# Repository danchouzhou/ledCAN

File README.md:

# ledCAN
A multipurpose buck converter with CAN interface.

## Clone the project
This project work with M0A21BSP submodule from Nuvoton corporation. You need to initialize submodules by passing ``--recurse-submodules`` to the ``git clone`` command.
```
git clone https://github.com/MIH-pi/ledCAN.git --recurse-submodules
```

## Prepare environment
1. Installing tools
```
sudo apt install kicad build-essential gcc-arm-none-eabi libtool libusb-1.0-0-dev
```
2. Build and install customize version of OpenOCD for Nuvoton devices
```
git clone https://github.com/OpenNuvoton/OpenOCD-Nuvoton.git
cd OpenOCD-Nuvoton
./bootstrap
./configure --enable-nulink
make
sudo make install
```

## Credits
We are thankful that [Nuvoton corporation](https://www.nuvoton.com) (MCU),[PANJIT](https://www.panjit.com.tw) (MOSFET), [EDOM Technology](https://www.edomtech.com) (MPS MPQ4569GQ) and [Texas Instruments](https://ti.com) (CAN SBC) provide samples and technical support.

## Datasheet
[Nuvoton NuMicro M0A21/M0A23](https://www.nuvoton.com/export/resource-files/TRM_M0A21_M0A23_Series_EN_Rev1.02.pdf)

## Reference documents

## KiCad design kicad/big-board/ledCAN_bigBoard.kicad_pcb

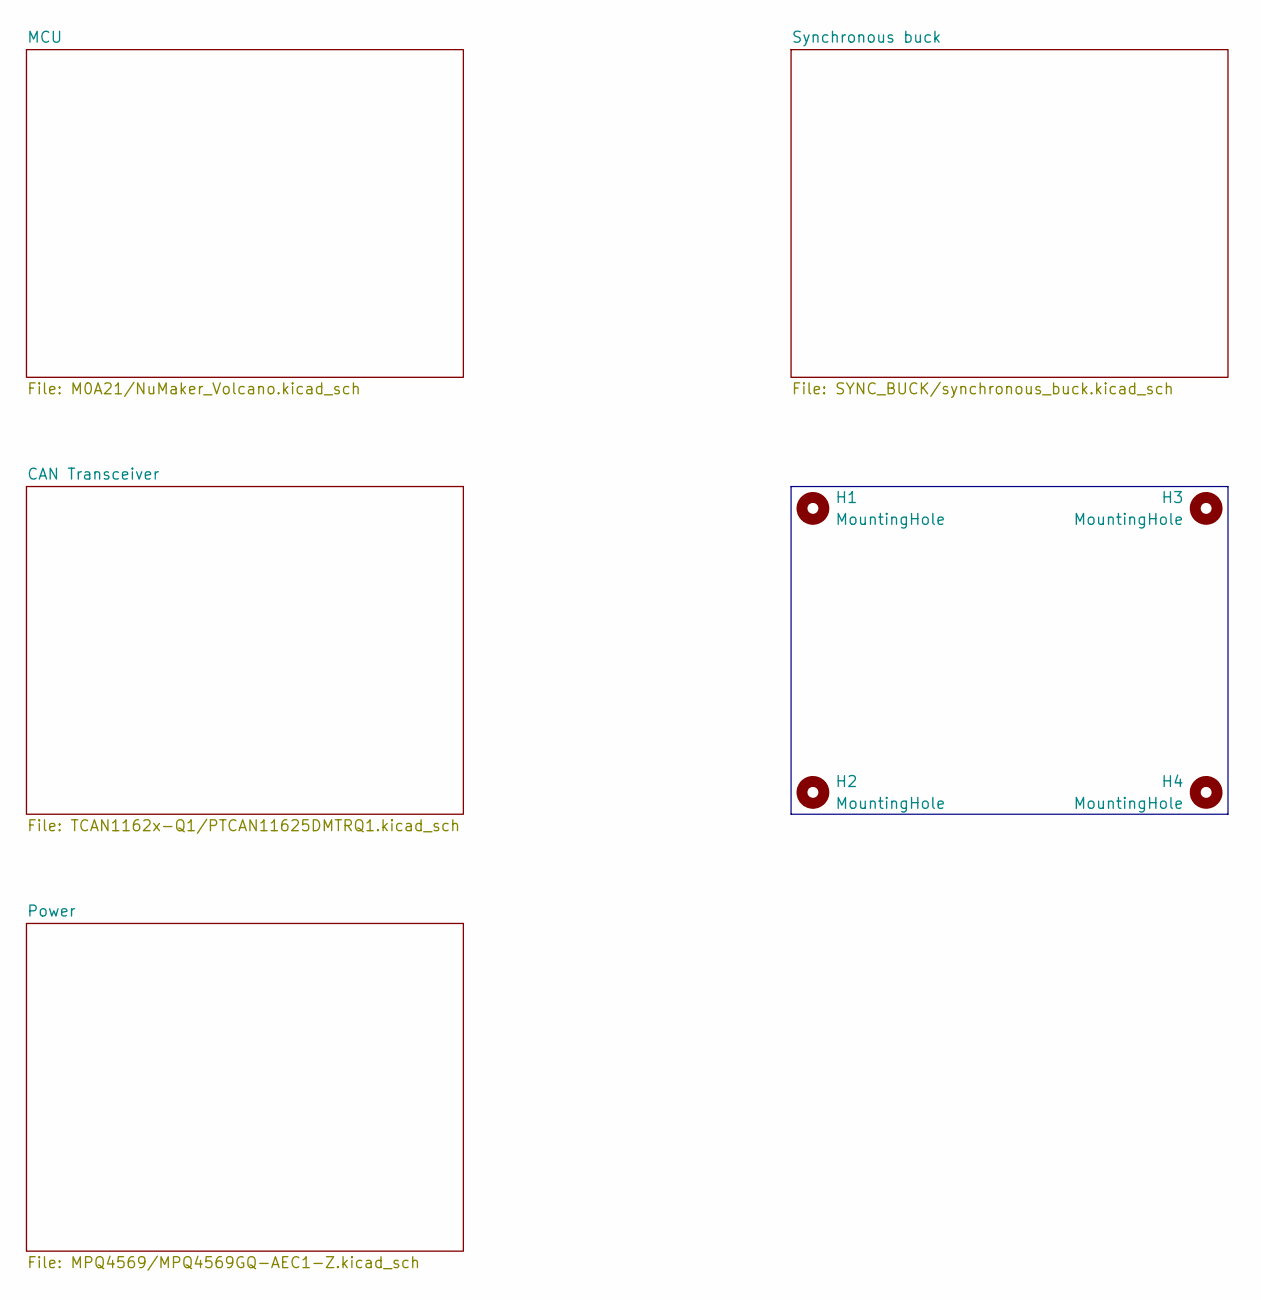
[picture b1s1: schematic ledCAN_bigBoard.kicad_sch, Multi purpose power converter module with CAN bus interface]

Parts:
H1, H2, H3, H4: MountingHole; MountingHole_3.2mm_M3

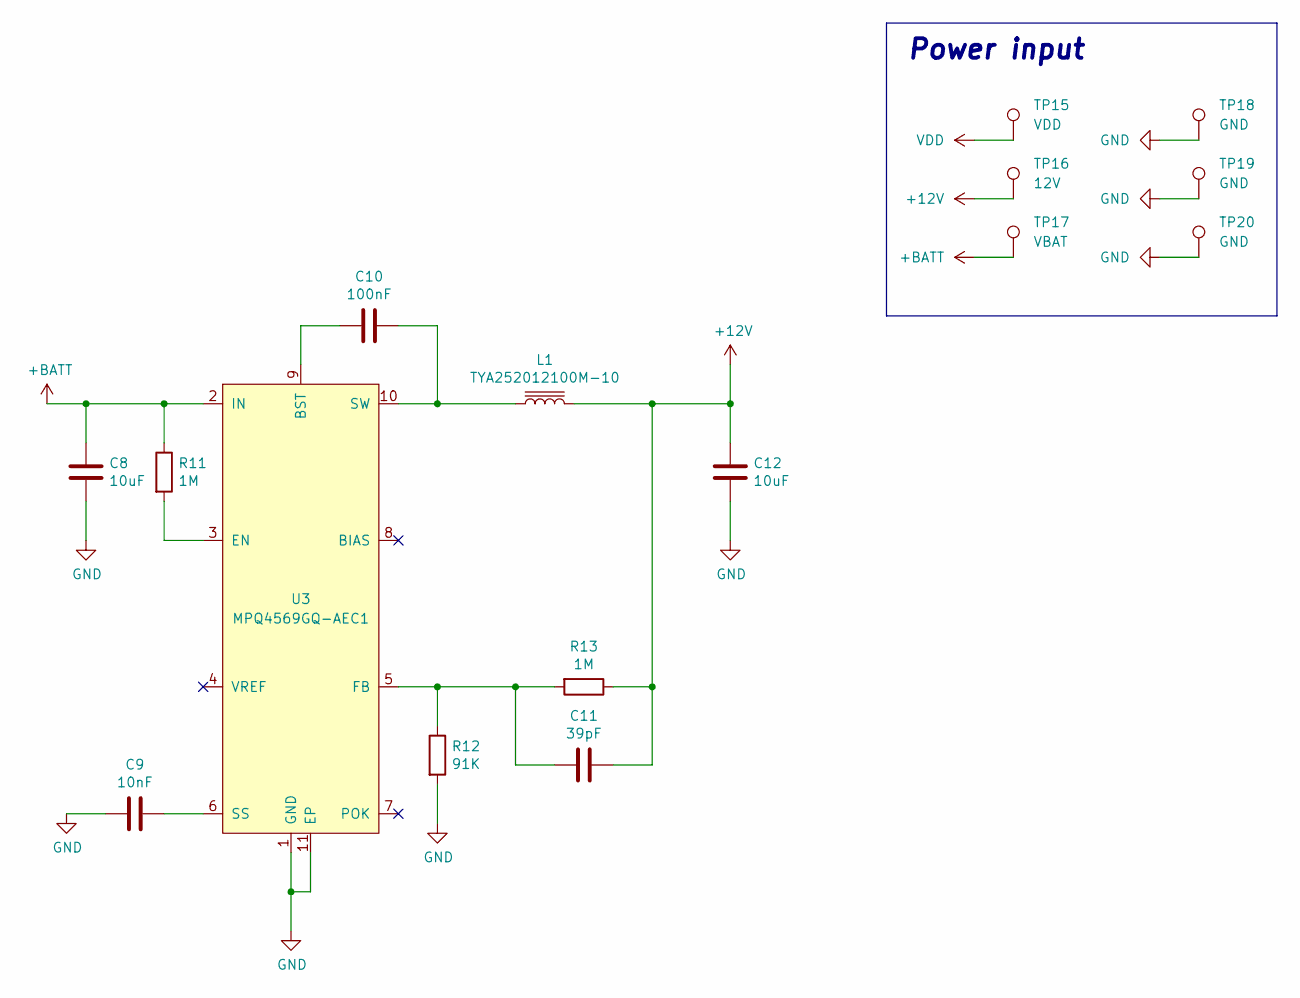
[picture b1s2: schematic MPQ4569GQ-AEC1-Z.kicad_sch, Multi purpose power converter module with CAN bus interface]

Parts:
C8: 10uF; C_1210_3225Metric
C9: 10nF; C_0603_1608Metric
C10: 100nF; C_0603_1608Metric
C11: 39pF; C_0603_1608Metric
C12: 10uF; C_0805_2012Metric
L1: TYA252012100M-10; tya252010-series
R11, R13: 1M; R_0603_1608Metric
R12: 91K; R_0603_1608Metric
TP15: VDD; TestPoint_Keystone_5005-5009_Compact
TP16: 12V; TestPoint_Keystone_5005-5009_Compact
TP17: VBAT; TestPoint_Keystone_5005-5009_Compact
TP18, TP19, TP20: GND; TestPoint_Keystone_5005-5009_Compact
U3: MPQ4569GQ-AEC1; QFN-10-1EP_3x3mm_P0.5mm_EP1.7x2.5mm

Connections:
+12V: C11.1, C12.1, L1.2, R13.1, TP16.1; also elsewhere on the board
+BATT: C8.1, R11.1, TP17.1, U3.2 (IN); also elsewhere on the board
unnamed: C9.1, U3.6 (SS)
unnamed: C10.1, L1.1, U3.10 (SW)
unnamed: C10.2, U3.9 (BST)
unnamed: C11.2, R12.1, R13.2, U3.5 (FB)
unnamed: R11.2, U3.3 (EN)

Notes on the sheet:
Power input

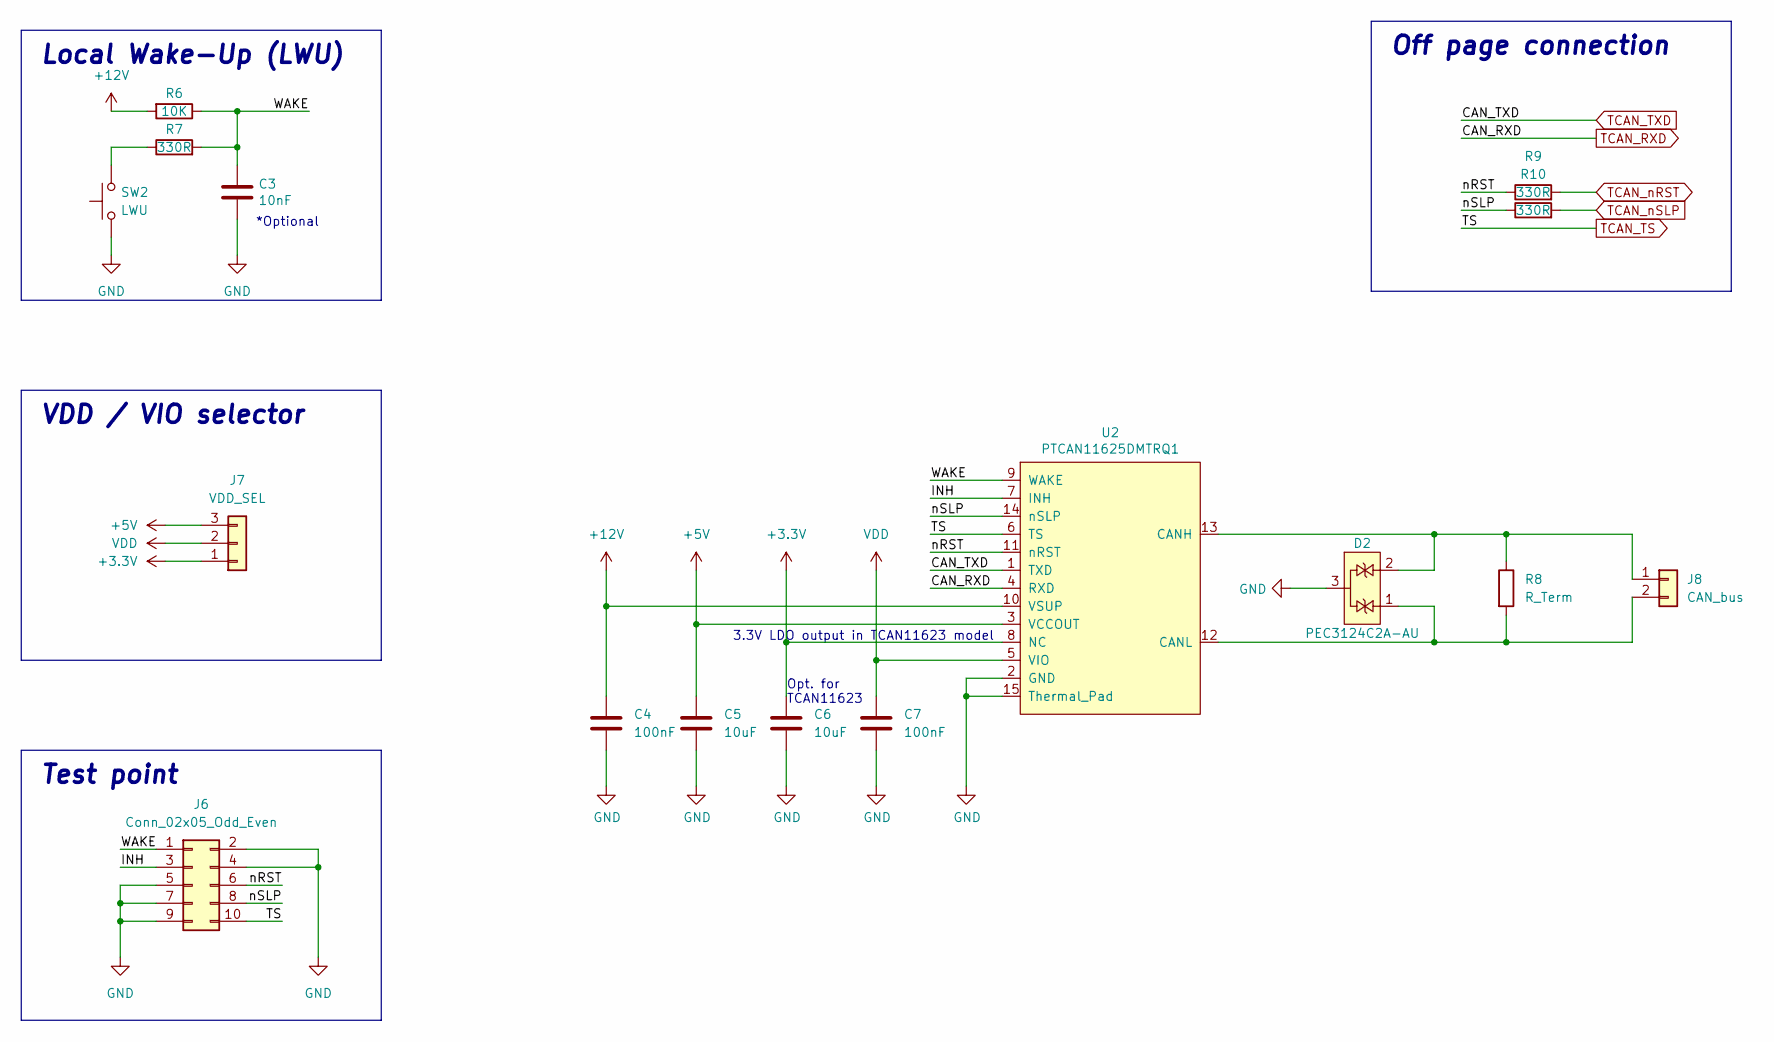
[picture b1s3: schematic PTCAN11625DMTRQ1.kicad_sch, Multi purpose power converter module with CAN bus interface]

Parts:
C3: 10nF; C_0603_1608Metric
C4, C7: 100nF; C_0603_1608Metric
C5, C6: 10uF; R_0805_2012Metric
D2: PEC3124C2A-AU; SOT-23; Manufacturer P/N PEC3124C2A-AU_R1_000A1
J6: Conn_02x05_Odd_Even; PinHeader_2x05_P2.54mm_Vertical
J7: VDD_SEL; PinHeader_1x03_P2.54mm_Vertical
J8: CAN_bus; PinHeader_1x02_P2.54mm_Vertical
R6: 10K; R_0603_1608Metric
R7, R9, R10: 330R; R_0603_1608Metric
R8: R_Term; R_1206_3216Metric
SW2: LWU; SW_PUSH_6mm
U2: PTCAN11625DMTRQ1; TI_VSON-14_4.5x3.0mm_DMT0014B_ThermalVias

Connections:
+3.3V: C6.1, J7.1, U2.8 (NC)
+5V: C5.1, J7.3, U2.3 (VCCOUT); also elsewhere on the board
+12V: C4.1, R6.2, U2.10 (VSUP); also elsewhere on the board
/CAN Transceiver/INH: J6.3, U2.7 (INH)
/CAN Transceiver/WAKE: C3.1, J6.1, R6.1, R7.2, U2.9 (WAKE)
/CAN Transceiver/nRST: J6.6, R9.1, U2.11 (nRST)
/CAN Transceiver/nSLP: J6.8, R10.1, U2.14 (nSLP)
unnamed: D2.1, J8.2, R8.2, U2.12 (CANL)
unnamed: D2.2, J8.1, R8.1, U2.13 (CANH)
unnamed: R7.1, SW2.2
TCAN_RXD: U2.4 (RXD); also elsewhere on the board
TCAN_TS: J6.10, U2.6 (TS); also elsewhere on the board
TCAN_TXD: U2.1 (TXD); also elsewhere on the board
TCAN_nRST: R9.2; also elsewhere on the board
TCAN_nSLP: R10.2; also elsewhere on the board

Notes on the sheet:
Local Wake-Up (LWU)
Test point
3.3V LDO output in TCAN11623 model
VDD / VIO selector
Off page connection
Opt. for TCAN11623
*Optional

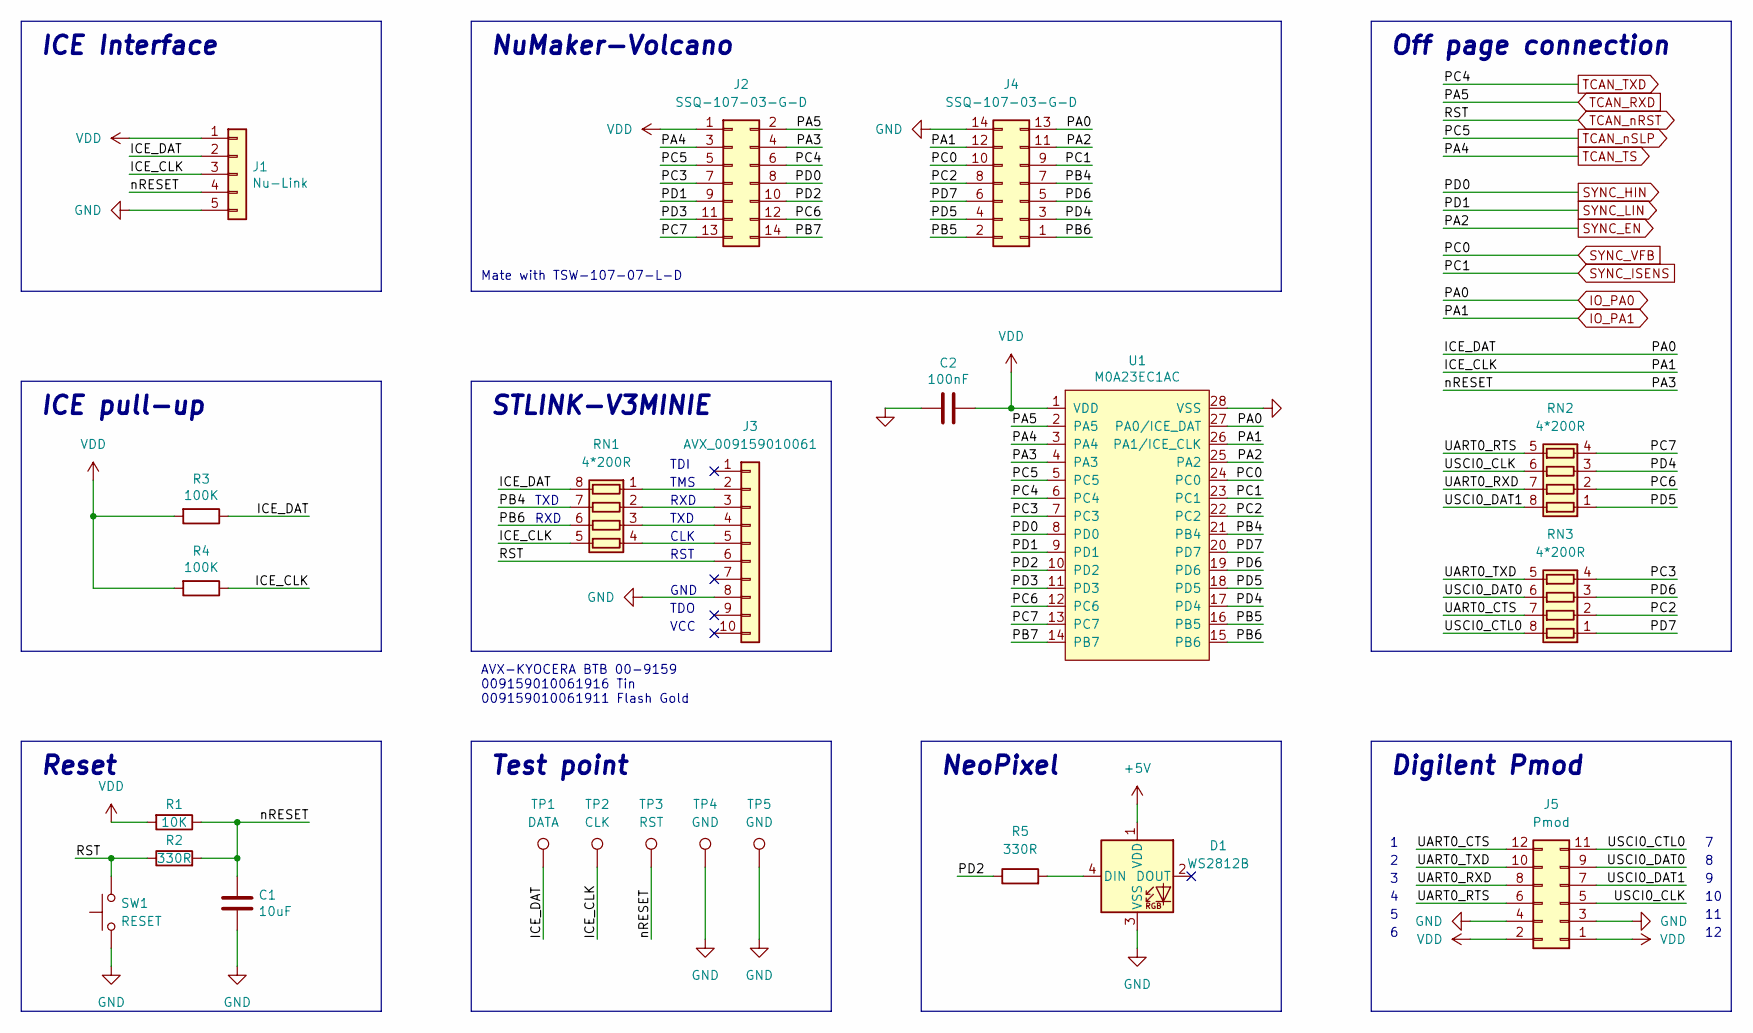
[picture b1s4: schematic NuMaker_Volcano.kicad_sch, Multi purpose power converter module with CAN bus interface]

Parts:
C1: 10uF; R_0603_1608Metric
C2: 100nF; C_0603_1608Metric
D1: WS2812B; LED_WS2812B_PLCC4_5.0x5.0mm_P3.2mm
J1: Nu-Link; PinHeader_1x05_P2.54mm_Vertical
J2, J4: SSQ-107-03-G-D; PinHeader_2x07_P2.54mm_Vertical
J3: AVX_009159010061; DebugEdge_2x05_Target
J5: Pmod; PinSocket_2x06_P2.54mm_Horizontal
R1: 10K; R_0603_1608Metric
R2, R5: 330R; R_0603_1608Metric
R3, R4: 100K; R_0603_1608Metric
RN1, RN2, RN3: 4*200R; R_Array_Convex_4x0603
SW1: RESET; SW_PUSH_6mm
TP1: DATA; TestPoint_Keystone_5005-5009_Compact
TP2: CLK; TestPoint_Keystone_5005-5009_Compact
TP3: RST; TestPoint_Keystone_5005-5009_Compact
TP4, TP5: GND; TestPoint_Keystone_5005-5009_Compact
U1: M0A23EC1AC; TSSOP-28_4.4x9.7mm_P0.65mm

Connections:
+5V: D1.1 (VDD); also elsewhere on the board
/MCU/PA3: C1.1, J1.4, J2.4, R1.1, R2.2, TP3.1, U1.4 (PA3)
/MCU/PB4: J4.7, RN1.7 (R2.2), U1.21 (PB4)
/MCU/PB5: J4.2, U1.16 (PB5)
/MCU/PB6: J4.1, RN1.6 (R3.2), U1.15 (PB6)
/MCU/PB7: J2.14, U1.14 (PB7)
/MCU/PC2: J4.8, RN3.2 (R2.1), U1.22 (PC2)
/MCU/PC3: J2.7, RN3.4 (R4.1), U1.7 (PC3)
/MCU/PC6: J2.12, RN2.2 (R2.1), U1.12 (PC6)
/MCU/PC7: J2.13, RN2.4 (R4.1), U1.13 (PC7)
/MCU/PD2: J2.10, R5.1, U1.10 (PD2)
/MCU/PD3: J2.11, U1.11 (PD3)
/MCU/PD4: J4.3, RN2.3 (R3.1), U1.17 (PD4)
/MCU/PD5: J4.4, RN2.1 (R1.1), U1.18 (PD5)
/MCU/PD6: J4.5, RN3.3 (R3.1), U1.19 (PD6)
/MCU/PD7: J4.6, RN3.1 (R1.1), U1.20 (PD7)
/MCU/UART0_CTS: J5.12, RN3.7 (R2.2)
/MCU/UART0_RTS: J5.6, RN2.5 (R4.2)
/MCU/UART0_RXD: J5.8, RN2.7 (R2.2)
/MCU/UART0_TXD: J5.10, RN3.5 (R4.2)
/MCU/USCI0_CLK: J5.5, RN2.6 (R3.2)
/MCU/USCI0_CTL0: J5.11, RN3.8 (R1.2)
/MCU/USCI0_DAT0: J5.9, RN3.6 (R3.2)
/MCU/USCI0_DAT1: J5.7, RN2.8 (R1.2)
IO_PA0: J1.2, J4.13, R3.1, RN1.8 (R1.2), TP1.1, U1.27 (PA0/ICE_DAT); also elsewhere on the board
IO_PA1: J1.3, J4.12, R4.1, RN1.5 (R4.2), TP2.1, U1.26 (PA1/ICE_CLK); also elsewhere on the board
unnamed: D1.4 (DIN), R5.2
unnamed: J3.2, RN1.1 (R1.1)
unnamed: J3.3, RN1.2 (R2.1)
unnamed: J3.4, RN1.3 (R3.1)
unnamed: J3.5, RN1.4 (R4.1)
SYNC_EN: J4.11, U1.25 (PA2); also elsewhere on the board
SYNC_HIN: J2.8, U1.8 (PD0); also elsewhere on the board
SYNC_ISENS: J4.9, U1.23 (PC1); also elsewhere on the board
SYNC_LIN: J2.9, U1.9 (PD1); also elsewhere on the board
SYNC_VFB: J4.10, U1.24 (PC0); also elsewhere on the board
TCAN_RXD: J2.2, U1.2 (PA5); also elsewhere on the board
TCAN_TS: J2.3, U1.3 (PA4); also elsewhere on the board
TCAN_TXD: J2.6, U1.6 (PC4); also elsewhere on the board
TCAN_nRST: J3.6, R2.1, SW1.2; also elsewhere on the board
TCAN_nSLP: J2.5, U1.5 (PC5); also elsewhere on the board

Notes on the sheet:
ICE Interface
TDI
NeoPixel
TDO
Test point
Mate with TSW-107-07-L-D
TMS
RXD
Off page connection
Digilent Pmod
GND
VCC
AVX-KYOCERA BTB 00-9159 009159010061916 Tin 009159010061911 Flash Gold
TXD
CLK
STLINK-V3MINIE
RST
NuMaker-Volcano
ICE pull-up
Reset

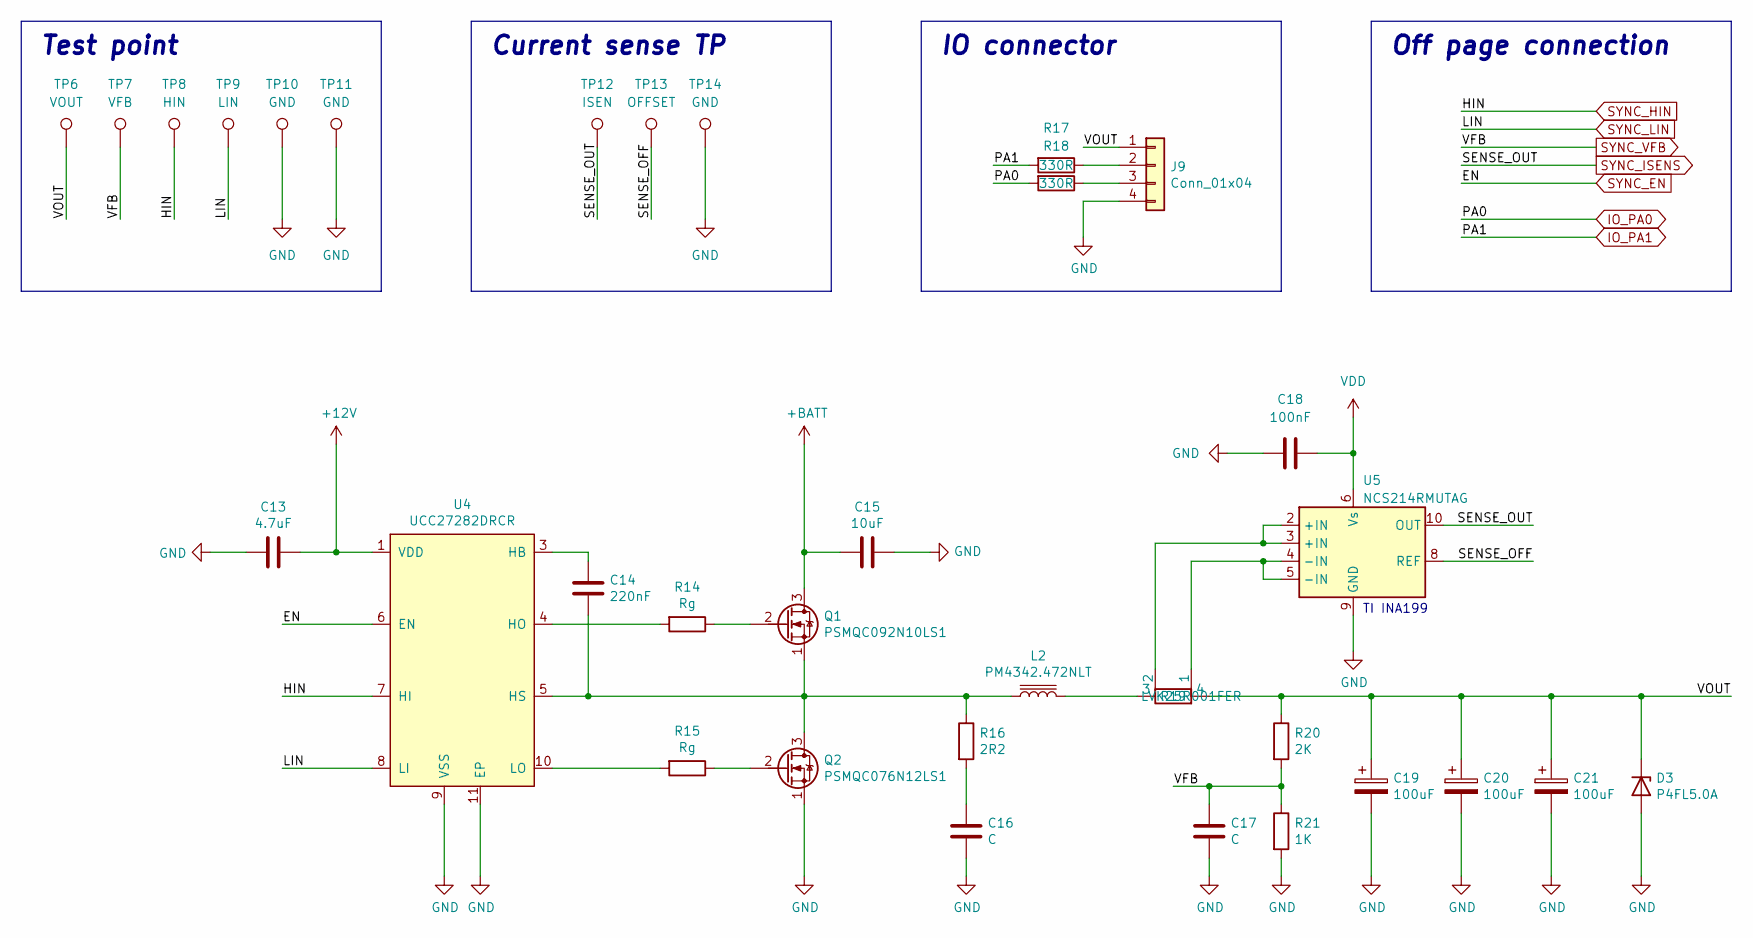
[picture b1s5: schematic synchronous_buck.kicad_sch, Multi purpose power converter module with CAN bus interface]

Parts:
C13: 4.7uF; C_0603_1608Metric
C14: 220nF; C_0603_1608Metric
C15: 10uF; C_1210_3225Metric
C16: C; C_1206_3216Metric
C17: C; C_0603_1608Metric
C18: 100nF; C_0603_1608Metric
C19, C20, C21: 100uF; CP_EIA-7343-31_Kemet-D
D3: P4FL5.0A; D_SOD-123F
J9: Conn_01x04; IO_CONN
L2: PM4342.472NLT; INDPM110100X400N
Q1: PSMQC092N10LS1; PANJIT_DFN5060-8L
Q2: PSMQC076N12LS1; PANJIT_DFN5060-8L
R14, R15: Rg; R_0603_1608Metric
R16: 2R2; R_1206_3216Metric_Pad1.30x1.75mm_HandSolder
R17, R18: 330R; R_0603_1608Metric
R19: LVK25R001FER; R_Shunt_Ohmite_LVK25
R20: 2K; R_0603_1608Metric
R21: 1K; R_0603_1608Metric
TP6: VOUT; TestPoint_Keystone_5005-5009_Compact
TP7: VFB; TestPoint_Keystone_5005-5009_Compact
TP8: HIN; TestPoint_Keystone_5005-5009_Compact
TP9: LIN; TestPoint_Keystone_5005-5009_Compact
TP10, TP11, TP14: GND; TestPoint_Keystone_5005-5009_Compact
TP12: ISEN; TestPoint_Keystone_5005-5009_Compact
TP13: OFFSET; TestPoint_Keystone_5005-5009_Compact
U4: UCC27282DRCR; Texas_DRC0010J_ThermalVias
U5: NCS214RMUTAG; UQFN-10_1.4x1.8mm_P0.4mm

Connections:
+12V: C13.1, U4.1 (VDD); also elsewhere on the board
+BATT: C15.2, Q1.3 (D); also elsewhere on the board
/Synchronous buck/SENSE_OFF: TP13.1, U5.8 (REF)
/Synchronous buck/VOUT: C19.1, C20.1, C21.1, D3.1 (A1), J9.1, R19.4, R20.1, TP6.1
IO_PA0: R18.2; also elsewhere on the board
IO_PA1: R17.2; also elsewhere on the board
unnamed: C14.1, U4.3 (HB)
unnamed: C14.2, L2.1, Q1.1 (S), Q2.3 (D), R16.1, U4.5 (HS)
unnamed: C16.1, R16.2
unnamed: J9.2, R17.1
unnamed: J9.3, R18.1
unnamed: L2.2, R19.3
unnamed: Q1.2 (G), R14.1
unnamed: Q2.2 (G), R15.1
unnamed: R14.2, U4.4 (HO)
unnamed: R15.2, U4.10 (LO)
unnamed: R19.1, U5.4 (-IN), U5.5 (-IN)
unnamed: R19.2, U5.2 (+IN), U5.3 (+IN)
SYNC_EN: U4.6 (EN); also elsewhere on the board
SYNC_HIN: TP8.1, U4.7 (HI); also elsewhere on the board
SYNC_ISENS: TP12.1, U5.10 (OUT); also elsewhere on the board
SYNC_LIN: TP9.1, U4.8 (LI); also elsewhere on the board
SYNC_VFB: C17.1, R20.2, R21.1, TP7.1; also elsewhere on the board

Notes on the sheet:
Off page connection
Current sense TP
IO connector
Test point
TI INA199

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
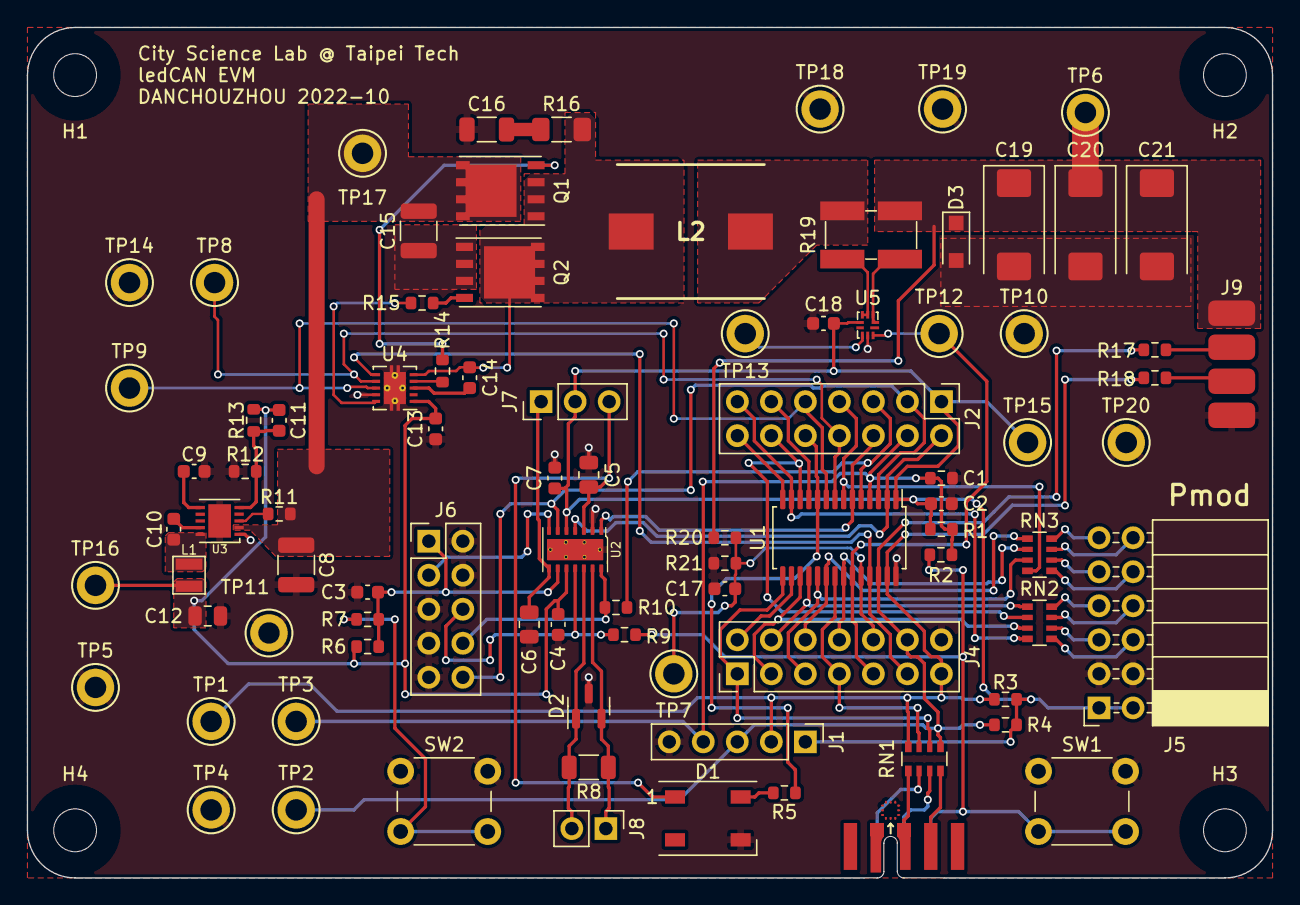
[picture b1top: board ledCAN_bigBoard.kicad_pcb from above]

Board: 2 copper layers, 93.0 x 63.5 mm, 92 parts (0 on the bottom side), 72 nets.

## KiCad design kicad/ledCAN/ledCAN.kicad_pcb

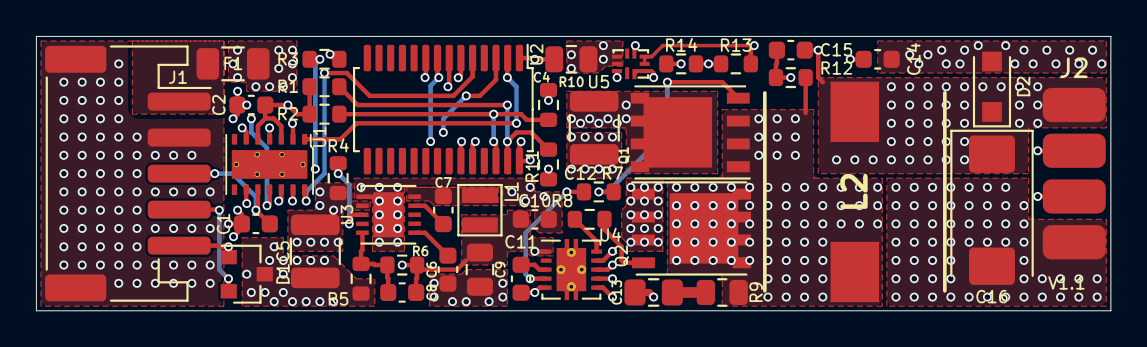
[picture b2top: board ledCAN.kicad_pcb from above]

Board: 4 copper layers, 59.7 x 15.2 mm, 43 parts (0 on the bottom side), 35 nets.

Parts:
C1, C7: 100nF; C_0603_1608Metric
C2: 10uF; C_0603_1608Metric
C4, C9: 10uF; C_0805_2012Metric
C5, C12: 10uF; C_1210_3225Metric
C6, C15: 10nF; C_0603_1608Metric
C8: 39pF; C_0603_1608Metric
C10: 4.7uF; C_0603_1608Metric
C11: 220nF; C_0603_1608Metric
C13: C; C_0805_2012Metric_Pad1.18x1.45mm_HandSolder
C14: 22pF; C_0603_1608Metric
C16: 100uF; CP_EIA-7343-31_Kemet-D
D1: PEC3124C2A-AU; SOT-23
D2: P4FL5.0A; D_SOD-123F
F1: Fuse; Fuse_1206_3216Metric
J1: Conn_01x05_MountingPin; JST_PH_S5B-PH-SM4-TB_1x05-1MP_P2.00mm_Horizontal
J2: Conn_01x04; IO_CONN
L1: TYA252012100M-10; tya252010-series
L2: SRP1038AA-R56M; INDPM110100X400N
Q1: PSMQC092N10LS1; PANJIT_DFN5060-8L
Q2: PSMQC076N12LS1; PANJIT_DFN5060-8L
R1, R2, R14: 100K; R_0603_1608Metric
R3: 10K; R_0603_1608Metric
R4, R6: 1M; R_0603_1608Metric
R5: 91K; R_0603_1608Metric
R7, R8: Rg; R_0603_1608Metric
R9: 2R2; R_0805_2012Metric
R10, R11: R; R_0603_1608Metric
R12: 36K; R_0603_1608Metric
R13: 200K; R_0603_1608Metric
U1: PTCAN11625DMTRQ1; TI_VSON-14_4.5x3.0mm_DMT0014B_ThermalVias
U2: M0A23EC1AC; TSSOP-28_4.4x9.7mm_P0.65mm
U3: MPQ4569GQ-AEC1; QFN-10-1EP_3x3mm_P0.5mm_EP1.7x2.5mm
U4: UCC27282DRCR; Texas_DRC0010J_ThermalVias
U5: NCS214RMUTAG; UQFN-10_1.4x1.8mm_P0.4mm

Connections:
+5V: C2.1, C4.1, R1.2, R2.2, U1.3, U1.5, U2.1, U5.6
+12V: C1.1, C8.1, C9.1, C10.1, J1.3, L1.2, R6.1, U1.10, U4.1, U4.6
+BATT: C5.1, C12.2, F1.2, Q1.3, R4.1, U3.2
/Synchronous rectification buck/VOUT: C15.1, C16.1, D2.1, J2.1, L2.2, R13.1, U5.4, U5.5
CAN0_RXD: U1.4, U2.3
CAN0_TXD: U1.1, U2.2
GND: C1.2, C2.2, C4.2, C5.2, C6.2, C9.2, C10.2, C12.1, C13.2, C14.2, C16.2, D1.3, D2.2, J1.2, J1.MP, J2.4, Q2.1, R3.2, R5.2, R14.2, U1.2, U1.15, U2.28, U3.1, U3.11, U4.9, U4.11, U5.8, U5.9
HIN: U2.24, U4.7
ISEN: U2.6, U5.10
LIN: U2.23, U4.8
unnamed: C6.1, U3.6
unnamed: C7.1, L1.1, U3.10
unnamed: C7.2, U3.9
unnamed: C8.2, R5.1, R6.2, U3.5
unnamed: C11.1, U4.3
unnamed: C11.2, L2.1, Q1.1, Q2.3, R9.1, R12.2, U4.5
unnamed: C13.1, R9.2
unnamed: C15.2, R12.1, U5.2, U5.3
unnamed: D1.1, J1.5, U1.12
unnamed: D1.2, J1.4, U1.13
unnamed: F1.1, J1.1
unnamed: J2.2, R10.1
unnamed: J2.3, R11.1
unnamed: Q1.2, R7.1
unnamed: Q2.2, R8.1
unnamed: R3.1, U1.9
unnamed: R4.2, U3.3
unnamed: R7.2, U4.4
unnamed: R8.2, U4.10
PA0: R1.1, R11.2, U2.27
PA1: R2.1, R10.2, U2.26
TCAN_TS: U1.6, U2.8
TCAN_nRST: U1.11, U2.9
TCAN_nSLP: U1.14, U2.5
VFB: C14.1, R13.2, R14.1, U2.7

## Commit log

2021-08-16 Add KiCad files
2021-08-17 Add submodule
2021-08-18 Add HelloWorld template
2021-08-18 Update Makefile
2021-08-24 Add ISP firmware
2021-08-25 Update schematic PDF
2021-08-26 Modify MFP setting
2021-08-26 Add README.md
2021-08-26 Fix silkscreen mistake, add labeling area
2021-08-27 Update main.c comment
2021-09-01 Fix MOSFET footprint mistake
2021-09-01 Add PCB back side image
2021-09-06 Add buck converter firmware
2021-09-06 Fix variable issues
2021-09-08 Change R6 value
2021-09-09 Add comment
2021-09-09 Add NeoPixel firmware
2021-09-10 Add strandtest
2021-09-11 Fix delayMicroseconds issue
2021-09-14 Improve some functions
2021-09-14 Review format and comments
2021-09-22 Update dead time control
2021-09-24 Add CAN_TxRx
2021-09-24 Fix some mistake
2021-09-27 Add DataFlashRead
2021-09-27 Add Makefile
2021-09-27 Update target name
2021-09-27 Improve config bits auto setup
2021-09-27 Rename directory
2021-09-29 Provide customize fuctions
2021-09-29 Add ledCAN
2021-09-29 Remove duplicate module clock setup
2021-09-29 Update comments
2021-10-01 Add breath and snake scroll effect
2021-10-01 Fix snake scroll issue
2021-10-02 Change inductor
2021-10-03 Change feedback circuit value
2021-10-03 Add netlist
2021-10-03 Update netlist
2021-10-04 Add buck converter
2021-10-05 Update A/D sample rate
2021-10-05 Add CAN ID read from data flash
2021-10-06 Add mode 6 read ADC0_CH1
2021-10-12 Provide mode 6 CAN TX function
2021-10-12 Update CAN data format
2021-10-12 Limit the max brightness
2021-10-15 Fix some bugs
2021-10-15 Add delay library
2021-10-15 Change transmit message object avoid from receive issues
2022-01-01 Change pin mode resolving method
2022-01-01 Update P gain
2022-05-08 Add servo
2022-06-06 Add CAN ID generating script
2022-06-07 Create Objects folder
2022-06-14 Fix GPIO mode while leaving Mode 6 (ADC)
2022-06-16 Add PWM setup
2022-06-16 Move MFP config prevent from programmer error
2022-06-16 Add servo test code
2022-06-16 Update comment
2022-06-16 Create servo library
2022-06-16 Add some servo function temporarily
2022-06-16 Add servo library
2022-06-16 Add servo_attached()
2022-06-20 Update issue date
2022-06-20 Fill the high two bytes in zero
2022-06-21 Add Nidec motor control
2022-06-21 Fix PWM_WGCTL sequence
2022-06-21 Add Nidec motor testing code
2022-06-21 Add Nidec motor controll
2022-06-21 Move delay library into Library path
2022-06-22 Move NeoPixel library into Library path
2022-06-22 Remove unused stuff
2022-06-22 Move servo library into Library path
2022-06-22 Move pid library into Library path
2022-06-22 Update the main functions
2022-06-22 Update PWM settings for buck converter
2022-06-22 Create Nidec library
2022-06-22 Fix PWM precaler setting
2022-06-22 Update main function
2022-06-22 Update the main function
2022-06-29 Fix CAN DLC overlay issue
2022-06-30 Stop the Nidec motor if lost the connection
2022-07-01 Update fabrication origin
2022-07-04 Change the sequence of clearing synchronize flag
2022-07-05 Add project template
2022-07-05 Add encoder
2022-07-06 Fix shift count overflow
2022-07-06 Pull up GPIO and fix data field issue
2022-07-06 Add inverting option for encoder
2022-07-29 Fix the max value issue of delayMicroseconds
2022-07-29 Fix the residual in breath mode
2022-08-01 Fix snake scroll mode data field issue
2022-08-01 Add python test code
2022-08-03 Add NuLibrary submodule
2022-08-03 Remove user library
2022-08-03 Use NuLibrary submodule
2022-08-03 Add arm_math_pid test code
2022-08-04 Add the feedback control example
2022-08-04 Update Makefile separate library and user code
2022-08-04 Add band gap reference read function
2022-08-04 Add the target value calculation by the internal band-gap
2022-08-05 Add analogRead()
2022-08-05 Update PID gain
2022-08-05 Update Makefile
    1. Separate BSP, library and user code to decrease compile time
2022-08-09 Use timer to get accurate sampling time
2022-08-09 Update PID config
2022-08-12 Update Mode 1 fill and clear sequence
2022-08-23 Move peripheral initialize into user_init
2022-08-29 Update submodule
2022-08-31 Add set sync ID
2022-08-31 Add python sample code
2022-08-31 Update firmware
2022-09-07 Update path
2022-09-07 Add big board
2022-09-07 Update to KiCad 6
2022-09-07 Update page settings
2022-09-07 Update schematic
2022-09-07 Remove kicad backups
2022-09-08 Update pinconfigure
2022-09-15 Add footprint table
2022-09-15 Update PCB
2022-09-15 Clear sync flag first in Nidec mode
2022-09-15 Fix the auto stop feature
2022-10-13 Ignore gerber files

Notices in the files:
kicad/big-board/M0A21/NuMaker_Volcano.kicad_sch:
DANCHOUZHOU © Danny Chou, all rights reserved.
